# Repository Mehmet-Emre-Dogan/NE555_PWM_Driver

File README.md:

# NE555_PWM_Driver
NE555 precision timer based IRFZ44N LED/motor driver design.
- No feedback loop
- Just open loop control
- No filter
- Bare PWM output
 
## PCB Design (DIP)

<div align="center">
 
### Schematic

### Front

### Back

 </div>

## PCB Design (SMD)

<div align="center">
 
### Schematic

### Front

### Back

 </div>

## PCB Images (SMD)

<div align="center">
 
### With Lamp

### Front

### Back

 </div>

## Oscilloscope Waveforms

<div align="center">

### General

### Whole Swing

### Ripple

### Noise

 </div>

 ### Conclusion

 - The theoratical frequency is consistent with experimental frequency
 - There is small discrepancies between the theoratical ripple and experimental ripple

## Simulation on LTSpice
  
 <div align="center">
 
### Circuit

### Waveforms

 </div>
 
 ## Prototype on Breadboard
  
 <div align="center">
 
 ### [Watch the video](https://youtu.be/RiIcqe25NVU)

 </div>

 ## References
https://circuitdigest.com/electronic-circuits/555-timer-pwm-generator-circuit

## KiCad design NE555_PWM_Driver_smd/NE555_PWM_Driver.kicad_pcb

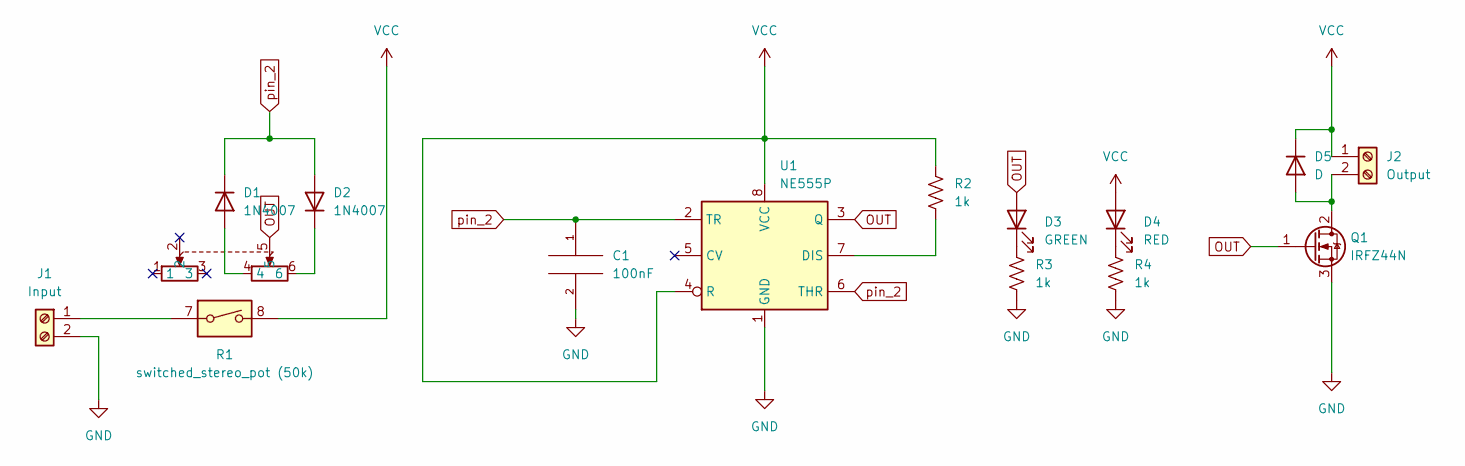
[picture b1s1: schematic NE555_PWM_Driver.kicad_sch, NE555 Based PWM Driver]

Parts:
C1: 100nF; C_0603_1608Metric_Pad1.08x0.95mm_HandSolder
D1, D2: 1N4007; D_SMB_Handsoldering
D3: GREEN; LED_D5.0mm_Clear
D4: RED; LED_D5.0mm_Clear
D5: D; D_SMC_Handsoldering
J1: Input; TerminalBlock_MetzConnect_Type101_RT01602HBWC_1x02_P5.08mm_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
J2: Output; TerminalBlock_MetzConnect_Type101_RT01602HBWC_1x02_P5.08mm_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
Q1: IRFZ44N; TO-220-3_Vertical
R1: switched_stereo_pot (50k); stereo_pot_with_switch
R2, R3, R4: 1k; R_0603_1608Metric_Pad0.98x0.95mm_HandSolder
U1: NE555P; SOIC-8-1EP_3.9x4.9mm_P1.27mm_EP2.41x3.3mm

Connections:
GND: C1.2, J1.2, Q1.3 (S), R3.2, R4.2, U1.1 (GND)
unnamed: D1.2 (A), R1.4
unnamed: D2.1 (K), R1.6
unnamed: D3.1 (K), R3.1
unnamed: D4.1 (K), R4.1
unnamed: D5.2 (A), J2.2, Q1.2 (D)
unnamed: J1.1, R1.7
unnamed: R2.2, U1.7 (DIS)
OUT: D3.2 (A), Q1.1 (G), R1.5, U1.3 (Q)
VCC: D4.2 (A), D5.1 (K), J2.1, R1.8, R2.1, U1.4 (R), U1.8 (VCC)
pin_2: C1.1, D1.1 (K), D2.2 (A), U1.2 (TR), U1.6 (THR)

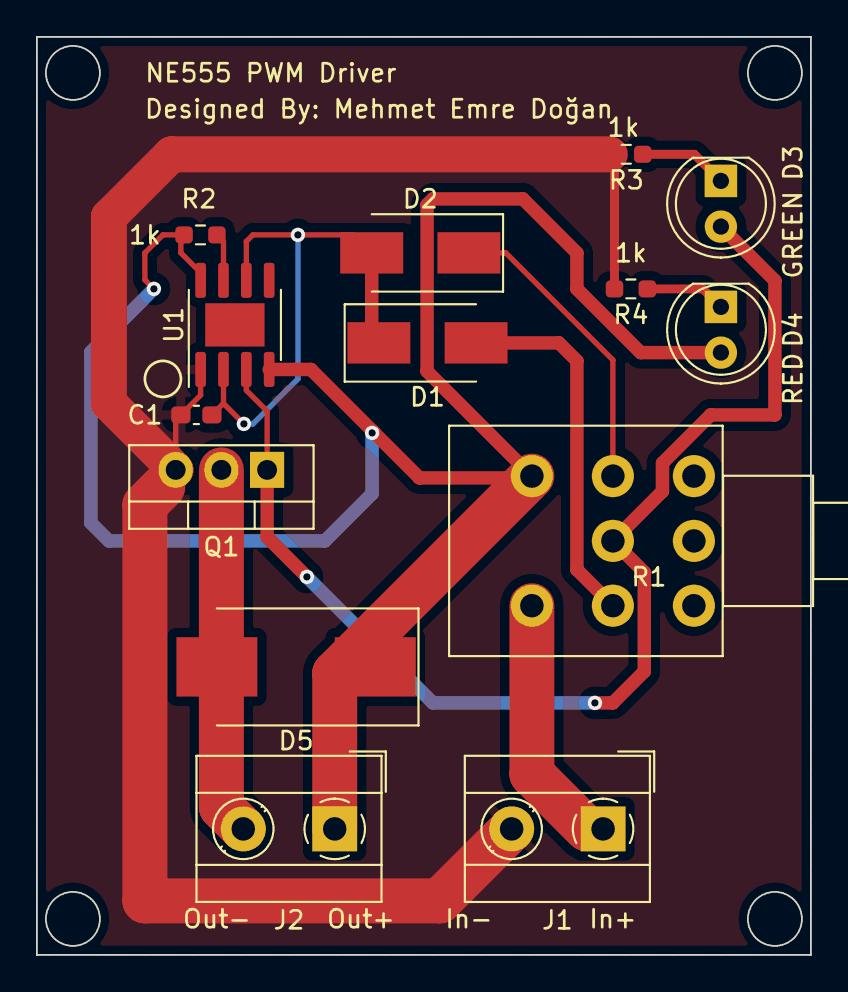
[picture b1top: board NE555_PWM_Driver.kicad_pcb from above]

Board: 2 copper layers, 43.0 x 51.0 mm, 14 parts (0 on the bottom side), 11 nets.

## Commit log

2022-03-19 added images
2022-03-19 added datasheets
2022-03-19 finished design
2022-03-19 image added, rotated images
2022-03-20 added i/o polarity on silkscreen
2022-07-31 designed SDM version of the card
2022-07-31 Update README.md
    fixed relative paths of the images
2022-08-06 filled top plane with ground
2022-08-06 added simulation images
2022-10-31 add pcb photos
2022-10-31 add scope images

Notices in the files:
NE555_PWM_Driver/NE555_PWM_Driver.kicad_sch:
creativecommons.org/licenses/by/4.0
License: CC BY 4.0
